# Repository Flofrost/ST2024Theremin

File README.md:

# Theremin

## Produit Minimum Viable (MVP)

    - 2 Antennas with their sensor
    - 1 Potentiometer per antenna to calibrate it
    - 1 3.5mm jack mono output
    - Project box (probably 3D printed, or bought off the shelf)

## Task 1

faire des recherches sur la theremin pour élargir le cahier des charges. ajouter des bargraph (led jolies)? ajouter un afficheur de la note jouée? intégrer un ampli et speaker intégré? possibilité ou pas de communiquer avec un ordinateur? etc...

## Task 2

commencer à déveloper un algorhithme pour le synthétiseur. objectif : lire un sample et le moduler pour le rejouer à la note qu'on veut (en C)

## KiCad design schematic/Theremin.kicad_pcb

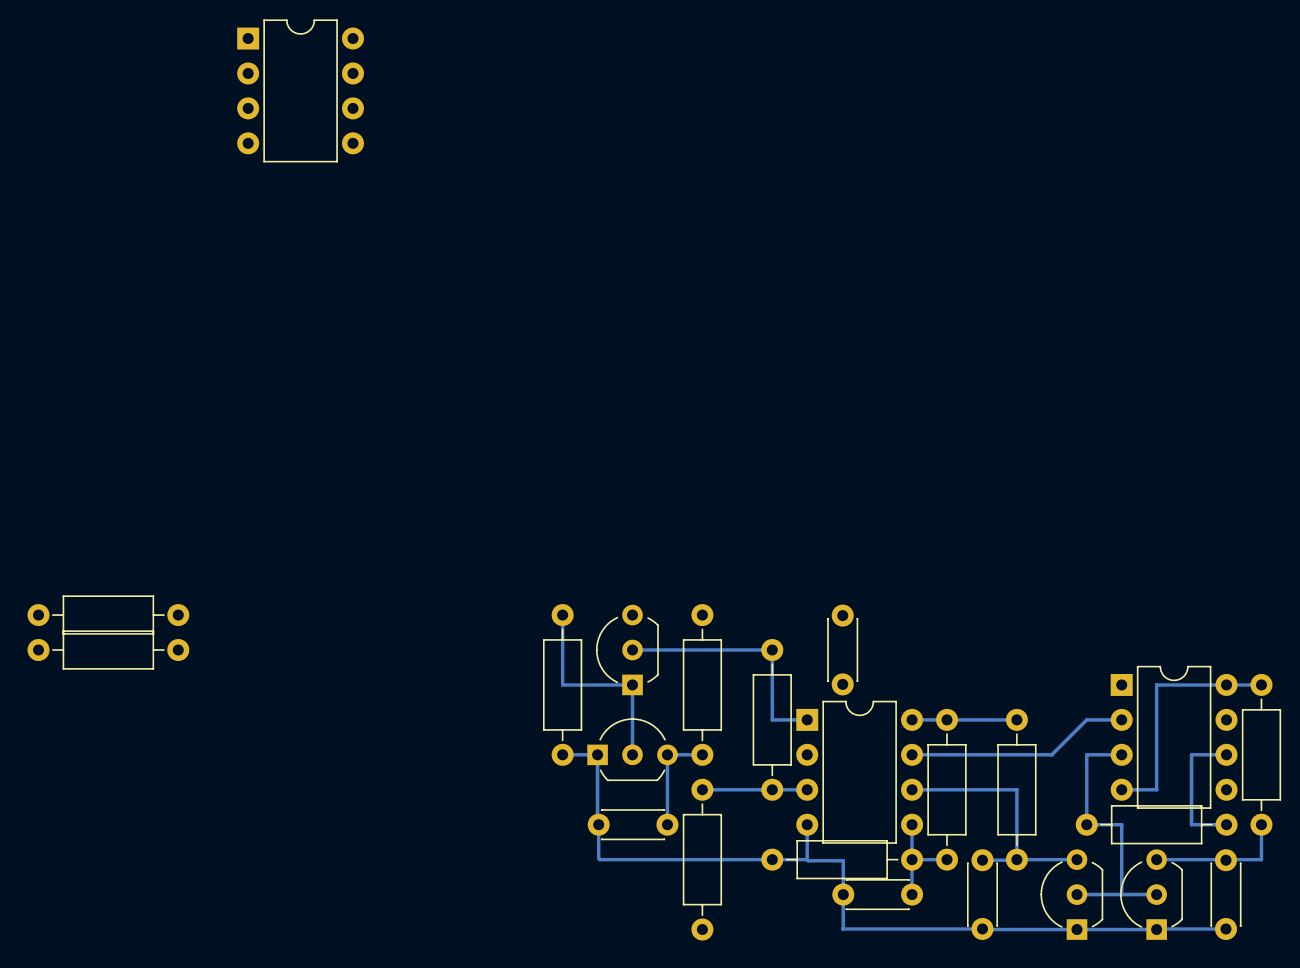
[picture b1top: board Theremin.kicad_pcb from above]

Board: 2 copper layers, 23 parts (0 on the bottom side), 13 nets.

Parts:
C2, C3: 1n; C_Disc_D4.3mm_W1.9mm_P5.00mm
C4: 1u; C_Disc_D4.3mm_W1.9mm_P5.00mm
C5: 100n; C_Disc_D4.3mm_W1.9mm_P5.00mm
C6: 20p; C_Disc_D4.3mm_W1.9mm_P5.00mm
Q1, Q2, Q3, Q4: 2N7000; TO-92_Inline_Wide
R1: 220; R_Axial_DIN0207_L6.3mm_D2.5mm_P10.16mm_Horizontal
R2: 10k; R_Axial_DIN0207_L6.3mm_D2.5mm_P10.16mm_Horizontal
R3, R6, R8, R9, R10: 100k; R_Axial_DIN0207_L6.3mm_D2.5mm_P10.16mm_Horizontal
R4: 1M; R_Axial_DIN0207_L6.3mm_D2.5mm_P10.16mm_Horizontal
R7: 56k; R_Axial_DIN0207_L6.3mm_D2.5mm_P10.16mm_Horizontal
R11, R12: ?; R_Axial_DIN0207_L6.3mm_D2.5mm_P10.16mm_Horizontal
U1: NE555D; DIP-8_W7.62mm
U2: AZV3002; DIP-8_W7.62mm
U3: MAX4392; DIP-8_W7.62mm

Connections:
+5V: Q4.3 (D), R2.1, R8.2, R10.2, R11.1, U1.4 (R), U1.8 (VCC), U2.8 (V+), U3.8 (V+)
DisMF: C6.1, Q1.3 (D), R10.1, U2.6 (-), U3.3 (+)
DisRF: C2.1, Q2.3 (D), R2.2, R3.1
GND: C2.2, C3.2, C4.2, C5.2, C6.2, Q1.1 (S), Q2.1 (S), Q3.1 (S), R6.2, R9.1, R12.2, U1.1 (GND), U2.4 (V-), U3.4 (V-)
unnamed: Q1.2 (G), Q2.2 (G), R1.1, U1.3 (Q)
unnamed: Q3.2 (G), Q4.1 (S), R6.1
unnamed: C3.1, Q4.2 (G), R4.2, U2.1
unnamed: R1.2, U1.6 (THR)
unnamed: R3.2, R4.1, U2.3 (+)
unnamed: C5.1, R8.1, R9.2, U2.5 (+)
OutFreq: C4.1, Q3.3 (D), R7.2
RaceEndFreq: U1.2 (TR), U2.7
ShieldF: U3.1, U3.2 (-)

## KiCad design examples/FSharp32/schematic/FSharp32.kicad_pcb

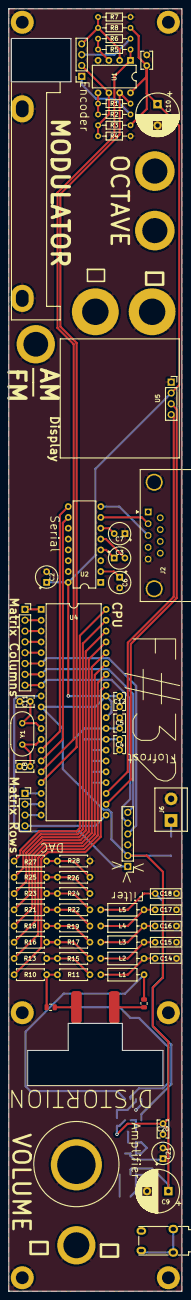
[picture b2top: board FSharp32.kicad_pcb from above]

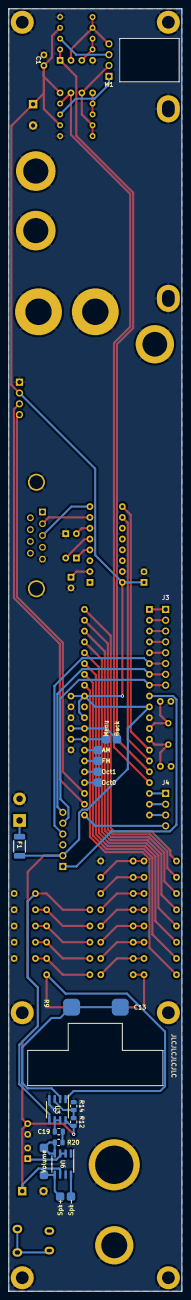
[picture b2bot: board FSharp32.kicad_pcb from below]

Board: 2 copper layers, 40.6 x 301.0 mm, 69 parts (7 on the bottom side), 66 nets.

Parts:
C1, C4, C5, C12, C20: 100n; C_Rect_L4.0mm_W2.5mm_P2.50mm
C2, C3, C6, C7, C21: 10u; CP_Radial_Tantal_D5.0mm_P2.50mm
C8, C11: 18p; C_Rect_L4.0mm_W2.5mm_P2.50mm
C9, C10: 100u; CP_Radial_D10.0mm_P5.00mm
C13, C19: C; C_0805_2012Metric
C14, C15, C16, C17, C18: 94p; C_Rect_L7.0mm_W2.0mm_P5.00mm
F1: Fuse; Fuse_2010_5025Metric
J1: PICkit2; PinHeader_1x06_P2.54mm_Vertical
J2: SerialPort; DSUB-9_Female_Horizontal_P2.77x2.84mm_EdgePinOffset7.70mm_H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
J3: MatrixCols; PinSocket_1x08_P2.54mm_Vertical
J4: MatrixRows; PinSocket_1x04_P2.54mm_Vertical
J5: AudioJack2_Ground; Jack_3.5mm_Lumberg_1503_07_Horizontal
J6: POWER; TerminalBlock_bornier-2_P5.08mm
L1, L2, L3, L4, L5: 56m; L_Axial_L6.6mm_D2.7mm_P10.16mm_Horizontal_Vishay_IM-2
M1: Stepper; PinSocket_1x04_P2.54mm_Vertical
R1, R5: 680k; R_Axial_DIN0204_L3.6mm_D1.6mm_P7.62mm_Horizontal
R2, R3, R4, R6, R7, R8: 10k; R_Axial_DIN0204_L3.6mm_D1.6mm_P7.62mm_Horizontal
R9, R20: 56k; R_0805_2012Metric
R10, R13, R16, R18, R21, R23, R25, R27, R28: 2k; R_Axial_DIN0207_L6.3mm_D2.5mm_P7.62mm_Horizontal
R11, R15, R17, R19, R22, R24, R26: 1k; R_Axial_DIN0207_L6.3mm_D2.5mm_P7.62mm_Horizontal
R12, R14: R; R_0805_2012Metric
U1: TLC3702; DIP-8_W7.62mm
U2: MAX232; DIP-16_W7.62mm
U3: MCP6002-xSN; SOIC-8_3.9x4.9mm_P1.27mm
U4: ATmega32-16P; DIP-40_W15.24mm
U5: SSD1306; PinSocket_1x04_P2.54mm_Vertical
U6: LM4861; SOIC-8_3.9x4.9mm_P1.27mm
Y1: 16M; Resonator-2Pin_W10.0mm_H5.0mm

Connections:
+5V: C1.1, C2.1, C9.1, C10.1, C12.1, C20.1, F1.1, J1.2, R3.2, R8.2, R12.1, U1.8 (V+), U2.16 (VCC), U3.8 (V+), U4.10 (VCC), U4.30 (AVCC), U4.32 (AREF), U5.2 (VCC), U6.6 (Vcc)
BackBtn: C5.1, U4.29 (PC7)
CLK: J1.5, J3.8, U4.8 (PB7)
DAC0: R27.1, U4.40 (PA0)
DAC1: R25.1, U4.39 (PA1)
DAC2: R23.1, U4.38 (PA2)
DAC3: R21.1, U4.37 (PA3)
DAC4: R18.1, U4.36 (PA4)
DAC5: R16.1, U4.35 (PA5)
DAC6: R13.1, U4.34 (PA6)
DAC7: R10.1, U4.33 (PA7)
GND: C1.2, C2.2, C4.2, C5.2, C6.2, C7.1, C8.1, C9.2, C10.2, C11.1, C12.2, C14.2, C15.2, C16.2, C17.2, C18.2, C20.2, C21.2, J1.3, J2.0 (PAD), J2.5, J6.2, R4.2, R7.2, R14.2, R28.2, U1.4 (V-), U2.15 (GND), U3.4 (V-), U4.11 (GND), U4.31 (GND), U5.1 (GND), U6.7 (GND)
MISO: J1.6, J3.7, U4.7 (PB6)
MOSI: J1.4, J3.6, U4.6 (PB5)
MenuBtn: C4.1, U4.28 (PC6)
unnamed: C13.2, R10.2, R11.1
unnamed: C14.1, L1.2, L2.1
unnamed: C15.1, L2.2, L3.1
unnamed: C16.1, L3.2, L4.1
unnamed: C17.1, L4.2, L5.1
unnamed: C19.1, R20.2
unnamed: J3.1, U4.1 (PB0)
unnamed: J3.2, U4.2 (PB1)
unnamed: J3.3, U4.3 (PB2)
unnamed: J3.4, U4.4 (PB3)
unnamed: J3.5, U4.5 (PB4)
unnamed: F1.2, J6.1
unnamed: L1.1, R9.2, U3.1
unnamed: M1.2 (-), R3.1, R4.1, U1.6 (-)
unnamed: M1.1, R2.2
unnamed: M1.3, R6.2
unnamed: R11.2, R13.2, R15.1
unnamed: R15.2, R16.2, R17.1
unnamed: R17.2, R18.2, R19.1
unnamed: R19.2, R21.2, R22.1
unnamed: R22.2, R23.2, R24.1
unnamed: R24.2, R25.2, R26.1
unnamed: R26.2, R27.2, R28.1
unnamed: J5.S, J5.T
unnamed: R5.2, R6.1, U1.3 (+)
unnamed: M1.4, R7.1, R8.1, U1.2 (-)
unnamed: R1.2, R2.1, U1.5 (+)
unnamed: C3.1, U2.4 (C2+)
unnamed: C3.2, U2.5 (C2-)
unnamed: J2.3, U2.8 (R2IN)
unnamed: J2.2, U2.7 (T2OUT)
unnamed: C6.1, U2.2 (VS+)
unnamed: C7.2, U2.6 (VS-)
unnamed: R12.2, R14.1, U3.3 (+)
unnamed: C18.1, L5.2, U3.5 (+)
unnamed: C19.2, U3.6 (-), U3.7
unnamed: C8.2, U4.13 (XTAL1), Y1.1
unnamed: C11.2, U4.12 (XTAL2), Y1.2
unnamed: C21.1, U6.2 (BP), U6.3 (+)
unnamed: R20.1, U6.4 (-)
PhaseA: R5.1, U1.1, U4.16 (PD2)
PhaseB: R1.1, U1.7, U4.17 (PD3)
RESET: J1.1, U4.9 (~RESET)
Row0: J4.1, U4.18 (PD4)
Row1: J4.2, U4.19 (PD5)
Row2: J4.3, U4.20 (PD6)
Row3: J4.4, U4.21 (PD7)
Rx: U2.9 (R2OUT), U4.14 (PD0)
SCL: U4.22 (PC0), U5.3 (SCL)
SDA: U4.23 (PC1), U5.4 (SDA)
Tx: U2.10 (T2IN), U4.15 (PD1)

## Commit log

2024-02-12 Decided on project : Theremin Started MVP Need to establish further specifications
2024-02-13 Added base scematic for theremin Need to tweak it to optimise it for theremin usage - Increase sensitivity - Increase stability - Use an RP2040
2024-02-15 (README) readme modified
2024-02-15 (dotfiles) gitignore added
2024-02-15 (C) c env configured
2024-02-15 (rust) rust env configured
2024-02-15 (rust) rust env deleted
2024-02-15 (rust) blink a led
2024-02-15 (dotfiles) gitignore updated
2024-02-15 (rust) cargo fix the code
2024-02-15 Continued schematic
2024-02-16 (examples) added and code updated
2024-02-16 delete
2024-02-16 add examples
2024-02-16 SCHEMATIC : continued schematic
2024-02-19 Started utility to extarct samples from wav files
2024-02-19 continued sample extraction script
2024-03-04 (MD) doc pour programmer sur le pico
2024-03-11 (rust) delete all about rust
2024-03-11 (pwm) improvements for PWM
2024-03-18 (pwm) pwm généré mais manque la signal sinusoïdale
2024-03-18 code + schematic + models??
